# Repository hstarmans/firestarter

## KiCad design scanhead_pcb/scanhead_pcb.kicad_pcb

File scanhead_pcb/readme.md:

Hexastorm - Scanhead pcb
========================================

https://www.hexastorm.com

PCB for a laser head. The pcb is connected to a cape on the beaglebone and the photodiode board.
There are components on both sides of the board.

# Status
Latest version still needs testing.

# Pinout mirror motor
The polygon motor is a modified Ricoh AF-1027/270 with a NBC3111 chip. The motor operates at
21000 RPM. The reflective polygon of this motor has been replaced with a
transparent prism. If you place the polygon in front of you and the pins point
toward you; the most right pin is pin one and the most left pin is pin 5. The
pinout is as follows; pin 1 is 24V, pin 2 is GND, pin 3 is GND, pin 4 is not
connected and pin 5 is PWM. The polygon motor can be connected with two
wires; GND and PWM. If it’s connected with two wires the GND should be
connected to the 24V supply voltage

# Schema

# Front Image

# Back Image

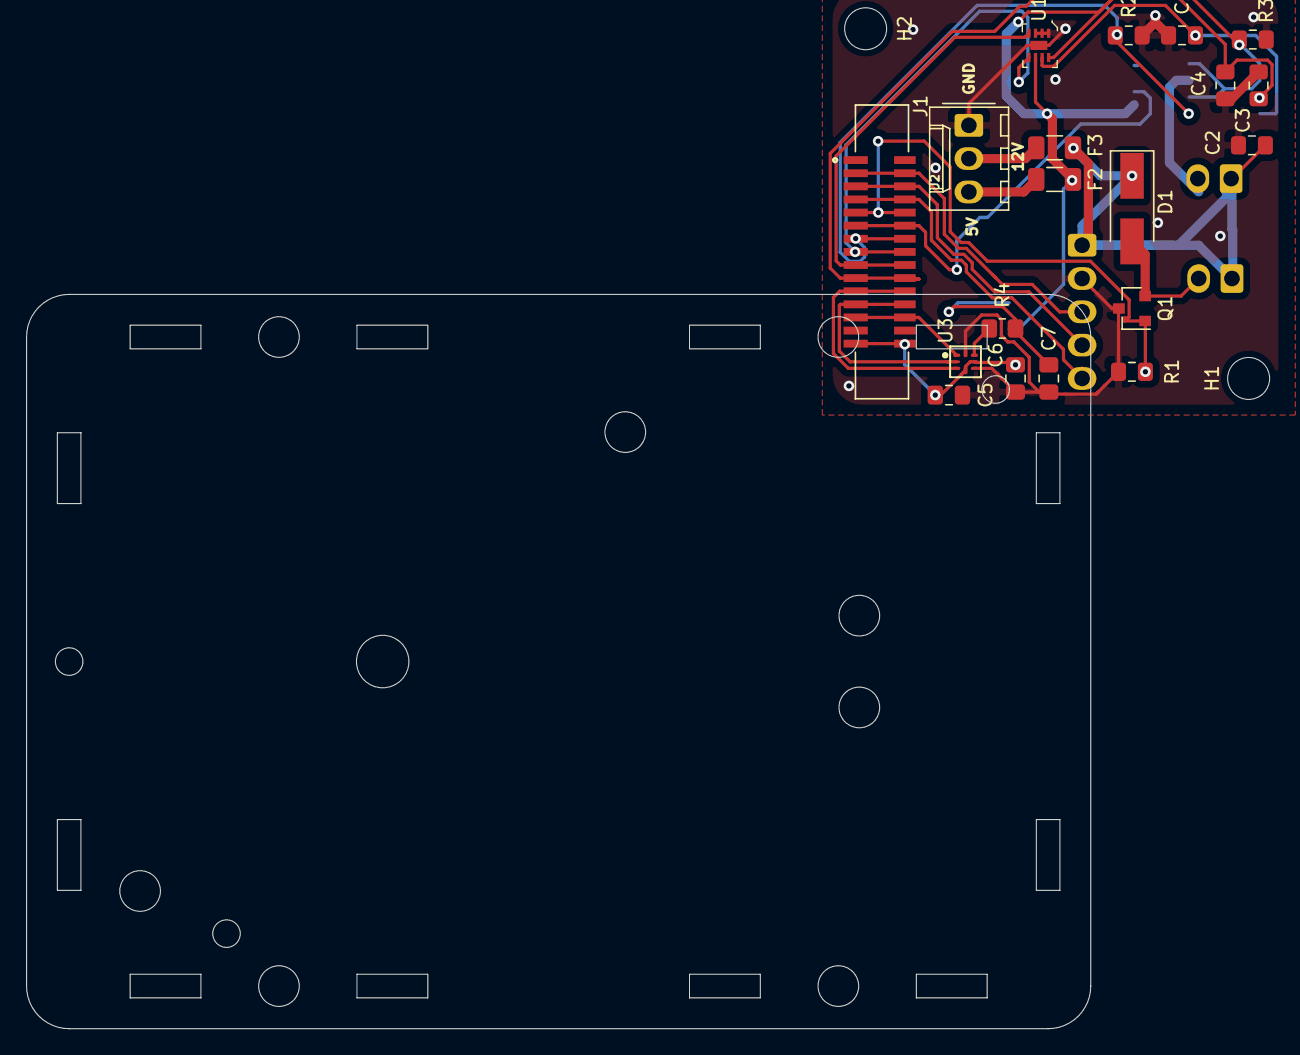
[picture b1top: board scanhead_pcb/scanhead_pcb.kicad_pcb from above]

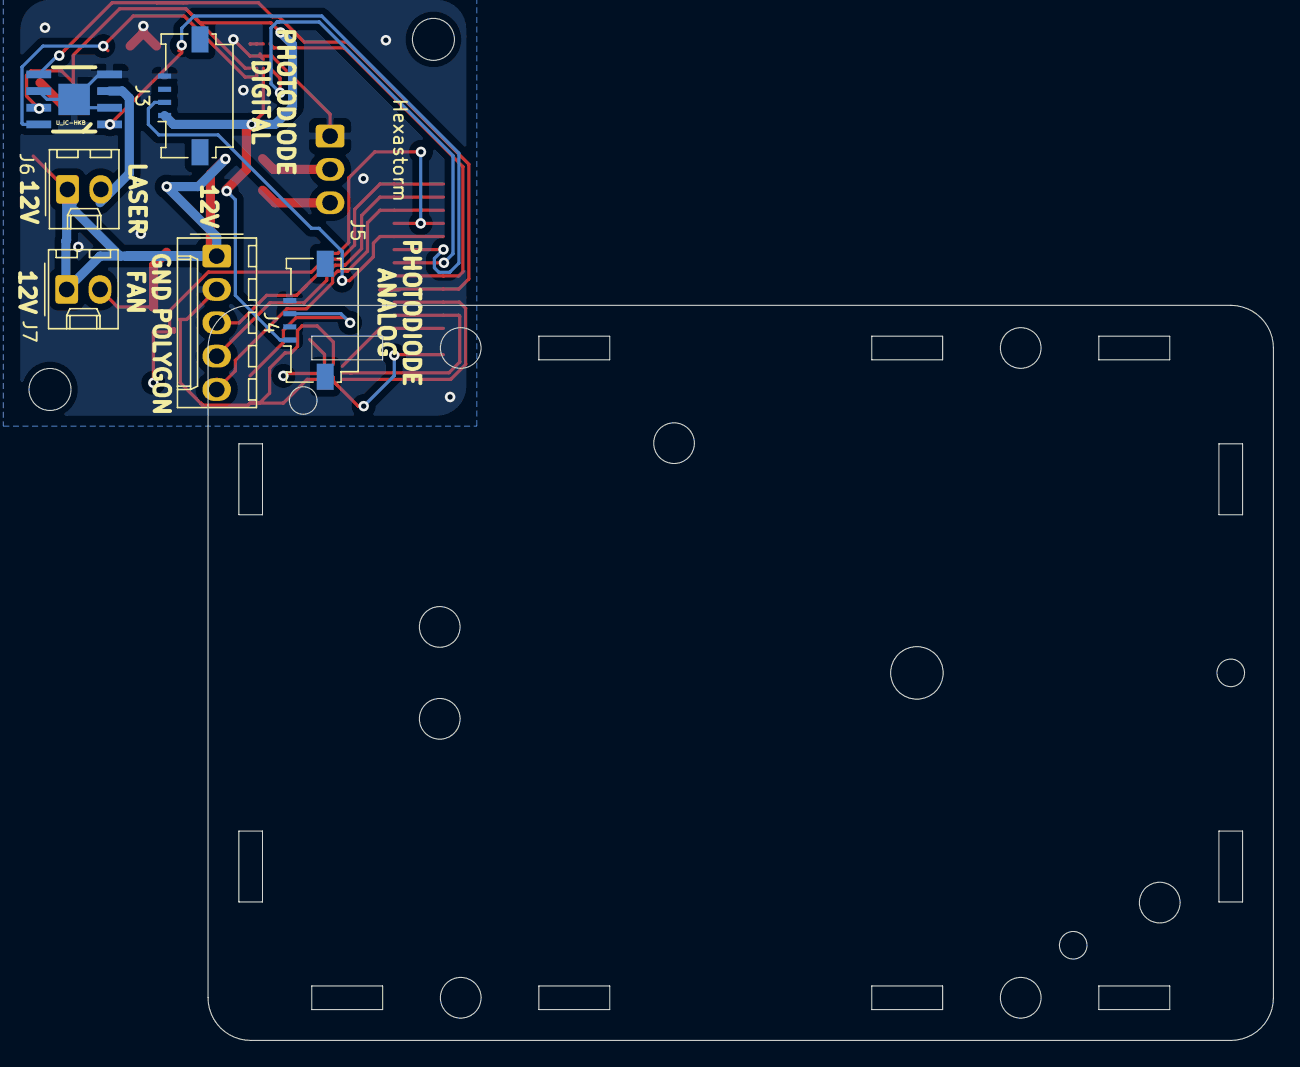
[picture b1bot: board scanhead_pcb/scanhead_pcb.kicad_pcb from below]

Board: 2 copper layers, 27 parts (6 on the bottom side), 23 nets.

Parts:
C1: 47nF; C_0805_2012Metric_Pad1.15x1.40mm_HandSolder
C2, C3: 1uF; C_0805_2012Metric_Pad1.15x1.40mm_HandSolder
C4: 0.1uF; C_0805_2012Metric_Pad1.15x1.40mm_HandSolder
C5, C6, C7: 1uF; C_0805_2012Metric_Pad1.18x1.45mm_HandSolder
D1: 50V_1A; D_SMA_Handsoldering
F2: 2A; Fuse_1206_3216Metric
F3: 3A; Fuse_1206_3216Metric
H1, H2: MountingHole; MountingHole_3.2mm_M3
J1: Screw_Terminal_01x03; Molex_KK-254_AE-6410-03A_1x03_P2.54mm_Vertical
J2: FPC 15 pin molex vertical; TE_1-1734248-5
J3, J5: FPC molex 4 pin; Molex_200528-0040_1x04-1MP_P1.00mm_Horizontal
J4: jumper wire 5 pin; Molex_KK-254_AE-6410-05A_1x05_P2.54mm_Vertical
J6, J7: jumper wire 2 pin; Molex_KK-254_AE-6410-02A_1x02_P2.54mm_Vertical
Q1: IRFML8244; SOT-23
R1, R2, R3: 10K; R_0805_2012Metric_Pad1.15x1.40mm_HandSolder
R4: 0K; R_0805_2012Metric_Pad1.20x1.40mm_HandSolder
U1: DIGIPOT_50K; TDFN-8-1EP
U2: U_IC-HKB; ICHKB
U3: NCD98011; Texas_Instruments-X2QFN8-0-0-0

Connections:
+3V3: C5.2, C6.1, J2.15, J2.15_1, U3.4, U3.6
+5V: C3.2, C4.2, F2.2, J3.1, J5.1, U1.6, U1.8, U2.7
+12V: C2.2, D1.1, F3.1, J4.1, J6.1, J7.1
ANALOG2: C7.1, J5.3, R4.1
DIGITAL1: J2.6, J2.6_1, J3.2
FAN_PWM: J2.5, J2.5_1, Q1.1, R1.1
GND: C1.1, C2.1, C3.1, C4.1, C5.1, C6.2, C7.2, J1.1, J3.4, J4.2, J5.4, Q1.3, R1.2, R2.1, R3.2, U1.1, U1.2, U1.3, U1.9, U2.2, U2.4, U2.6, U2.9, U3.5, U3.8
IC_HB_PWM1: J2.10, J2.10_1, R3.1, U2.5
IC_HB_PWM2: J2.7, J2.7_1, R2.2, U2.1
LDK: J6.2, U2.3
unnamed: D1.2, J7.2, Q1.2
unnamed: F2.1, J1.3
unnamed: F3.2, J1.2
unnamed: R4.2, U3.7
POLY_EN: J2.2, J2.2_1, J4.3
POLY_PWM: J2.4, J2.4_1, J4.5
POLY_READY: J2.3, J2.3_1, J4.4
POT_SCL: J2.8, J2.8_1, U1.5
POT_SDA: J2.9, J2.9_1, U1.4
POT_W: C1.2, U1.7, U2.8
SPI_CLK: J2.11, J2.11_1, U3.3
SPI_CSN: J2.13, J2.13_1, U3.1
SPI_OUT: J2.12, J2.12_1, U3.2

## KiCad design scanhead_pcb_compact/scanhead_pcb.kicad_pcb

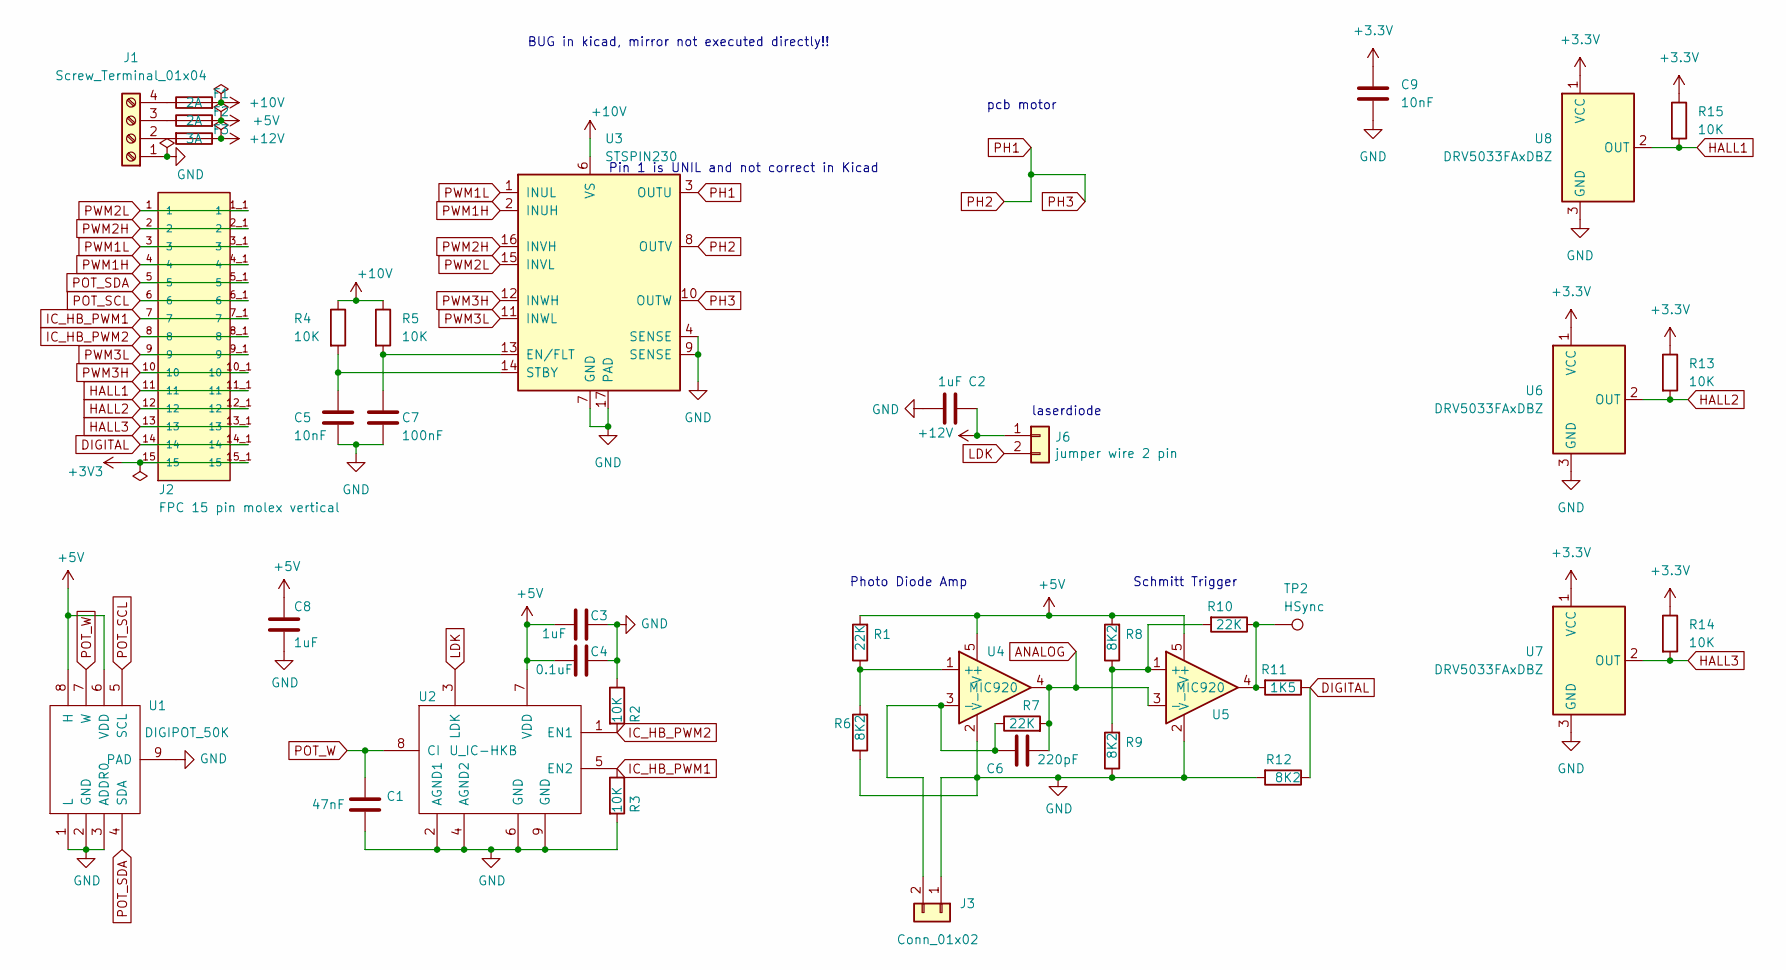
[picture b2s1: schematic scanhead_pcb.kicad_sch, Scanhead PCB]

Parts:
C1: 47nF; C_0805_2012Metric_Pad1.18x1.45mm_HandSolder
C2, C3, C8: 1uF; C_0805_2012Metric_Pad1.18x1.45mm_HandSolder
C4: 0.1uF; C_0805_2012Metric_Pad1.18x1.45mm_HandSolder
C5, C9: 10nF; C_0805_2012Metric_Pad1.18x1.45mm_HandSolder
C6: 220pF; C_0805_2012Metric_Pad1.18x1.45mm_HandSolder
C7: 100nF; C_0805_2012Metric_Pad1.18x1.45mm_HandSolder
F1, F2: 2A; Fuse_1206_3216Metric
F3: 3A; Fuse_1206_3216Metric
J1: Screw_Terminal_01x04; Molex_KK-254_AE-6410-04A_1x04_P2.54mm_Vertical
J2: FPC 15 pin molex vertical; TE_1-1734248-5
J3: Conn_01x02; PinHeader_1x02_P2.54mm_Vertical
J6: jumper wire 2 pin; Molex_KK-254_AE-6410-02A_1x02_P2.54mm_Vertical
R1, R7, R10: 22K; R_0805_2012Metric_Pad1.20x1.40mm_HandSolder
R2, R3, R4, R5, R13, R14, R15: 10K; R_0805_2012Metric_Pad1.20x1.40mm_HandSolder
R6, R8, R9, R12: 8K2; R_0805_2012Metric_Pad1.20x1.40mm_HandSolder
R11: 1K5; R_0805_2012Metric_Pad1.20x1.40mm_HandSolder
TP2: HSync; TestPoint_Pad_D1.0mm
U1: DIGIPOT_50K; TDFN-8-1EP
U2: U_IC-HKB; ICHKB
U3: STSPIN230; VQFN-16-1EP_3x3mm_P0.5mm_EP1.8x1.8mm
U4, U5: MIC920; SOT-353_SC-70-5_Handsoldering
U6, U7, U8: DRV5033FAxDBZ; SOT-23

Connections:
+5V: C3.2, C4.2, C8.1, F2.2, R1.2, R8.2, U1.6 (VDD), U1.8 (H), U2.7 (VDD), U4.5 (V+), U5.5 (V+)
+10V: F1.2, R4.1, R5.1, U3.6 (VS)
+12V: C2.2, F3.1, J6.1
ANALOG: C6.1, R7.2, U4.4, U5.3 (-)
DIGITAL: J2.14, J2.14_1 (14), R11.1, R12.1
GND: C1.1, C2.1, C3.1, C4.1, C5.2, C7.2, C8.2, C9.2, J1.1, J3.1, R2.1, R3.2, R6.1, R9.1, R12.2, U1.1 (L), U1.2 (GND), U1.3 (ADDR0), U1.9 (PAD), U2.2 (AGND1), U2.4 (AGND2), U2.6 (GND), U2.9 (GND), U3.4 (SENSE), U3.7 (GND), U3.9 (SENSE), U3.17 (PAD), U4.2 (V-), U5.2 (V-), U6.3 (GND), U7.3 (GND), U8.3 (GND)
HALL1: J2.11, J2.11_1 (11), R15.2, U8.2 (OUT)
HALL2: J2.12, J2.12_1 (12), R13.2, U6.2 (OUT)
HALL3: J2.13, J2.13_1 (13), R14.2, U7.2 (OUT)
IC_HB_PWM1: J2.7, J2.7_1 (7), R3.1, U2.5 (EN2)
IC_HB_PWM2: J2.8, J2.8_1 (8), R2.2, U2.1 (EN1)
LDK: J6.2, U2.3 (LDK)
unnamed: C5.1, R4.2, U3.14 (STBY)
unnamed: C6.2, J3.2, R7.1, U4.3 (-)
unnamed: C7.1, R5.2, U3.13 (EN/FLT)
unnamed: F1.1, J1.4
unnamed: F2.1, J1.3
unnamed: F3.2, J1.2
unnamed: R1.1, R6.2, U4.1 (+)
unnamed: R10.1, R11.2, TP2.1, U5.4
unnamed: R8.1, R9.2, R10.2, U5.1 (+)
PH1: U3.3 (OUTU), U3.8 (OUTV), U3.10 (OUTW)
POT_SCL: J2.6, J2.6_1 (6), U1.5 (SCL)
POT_SDA: J2.5, J2.5_1 (5), U1.4 (SDA)
POT_W: C1.2, U1.7 (W), U2.8 (CI)
PWM1H: J2.4, J2.4_1 (4), U3.2 (INUH)
PWM1L: J2.3, J2.3_1 (3), U3.1 (INUL)
PWM2H: J2.2, J2.2_1 (2), U3.16 (INVH)
PWM2L: J2.1, J2.1_1 (1), U3.15 (INVL)
PWM3H: J2.10, J2.10_1 (10), U3.12 (INWH)
PWM3L: J2.9, J2.9_1 (9), U3.11 (INWL)

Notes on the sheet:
pcb motor
Photo Diode Amp
BUG in kicad, mirror not executed directly!!
Schmitt Trigger
laserdiode
Pin 1 is UNIL and not correct in Kicad

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
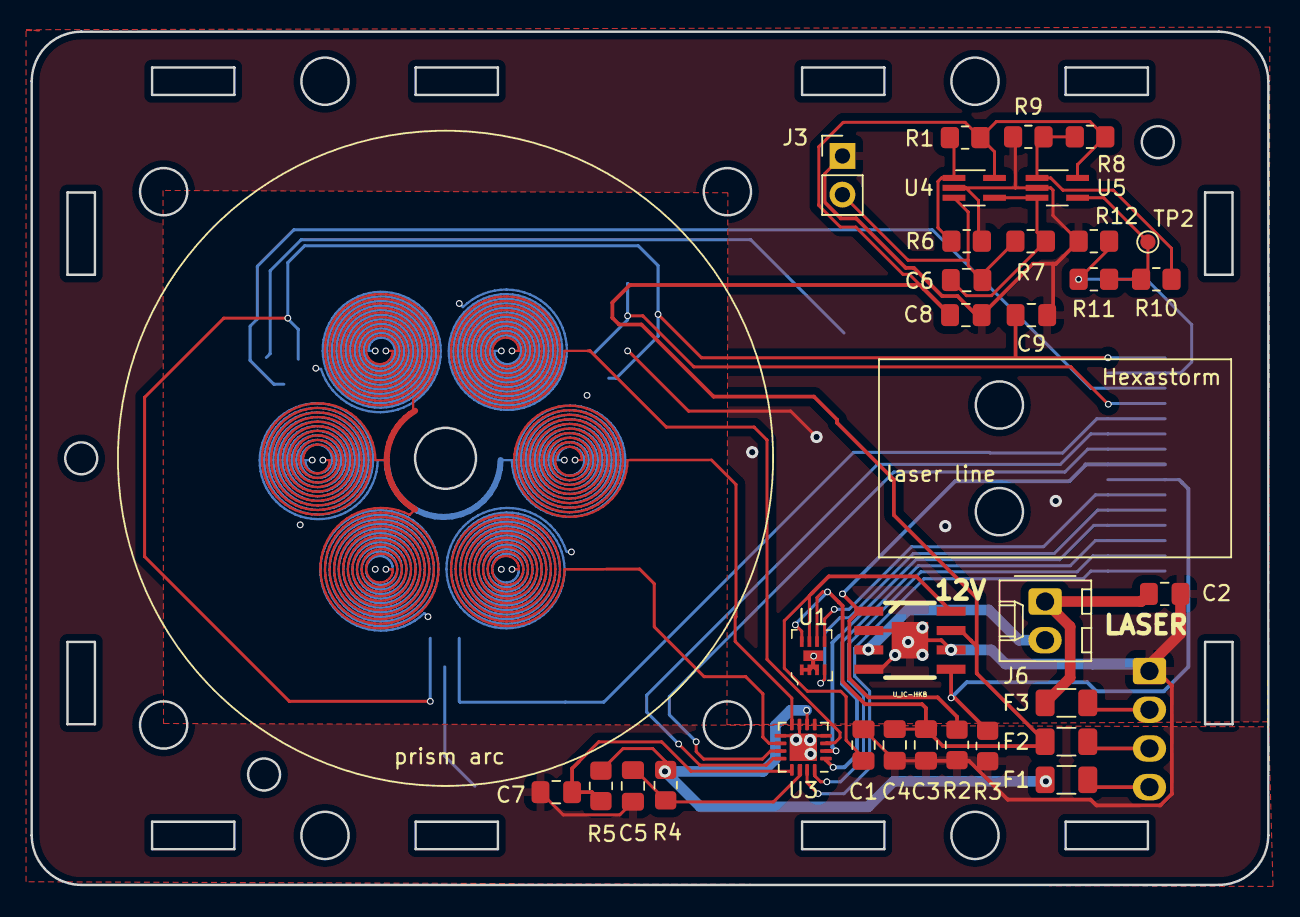
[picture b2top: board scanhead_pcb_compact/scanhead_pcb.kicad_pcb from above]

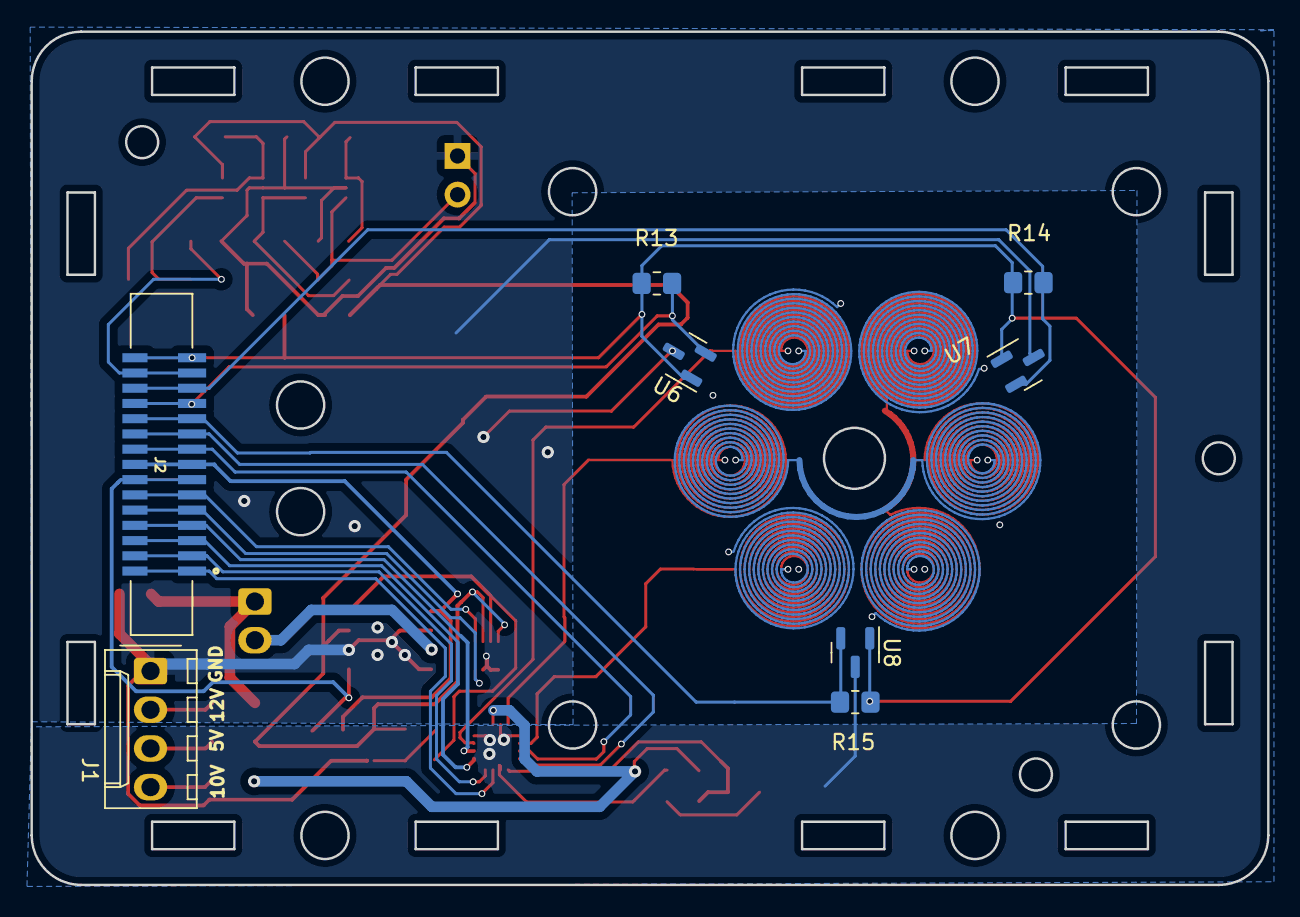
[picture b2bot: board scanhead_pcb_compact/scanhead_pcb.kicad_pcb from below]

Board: 4 copper layers, 81.2 x 56.0 mm, 40 parts (8 on the bottom side), 32 nets.
